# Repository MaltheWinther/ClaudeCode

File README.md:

# ClaudeCode

Testing Claude Code integration with GitHub.

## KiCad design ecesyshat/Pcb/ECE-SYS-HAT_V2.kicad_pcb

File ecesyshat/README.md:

# EceSysHat

This repo contains material for the ECE SYS HAT with the following devices:

* Six push-buttons
* Three LEDs
* An OLED Display
* An BMI160 Accelerometer / Gyro

### Documents

Contains pdf documentation, schematics

### PCB

Contains KiCad files for schematic and PCB

### TestPrograms

Contains small test programs to check correct assembly

Remember to enable i2c and spi with 'raspi_config' and install Libraries before running them. 

### Install Libraries 

#### Dependencies

To build and install the included libraries one needs to install some dependencies.

Run the following to install needed dependencies:

```bash
sudo apt update 
sudo apt install build-essential cmake git
```

#### Enabling i2c and spi 

As the oled screen communicates with the rpi using i2c, and the gyroscope communicates with the rpi using spi, one needs to enable those interfaces.

```bash
sudo raspi-config nonint do_i2c 0
sudo raspi-config nonint do_spi 0
```

#### Building and Installing

Enter Libraries dir:

```bash
cd Libraries/
```

You should now be able to run the following, to build and install the project.

```bash
cmake -S . -B build
cmake --build build
sudo cmake --install build --prefix /usr/
```

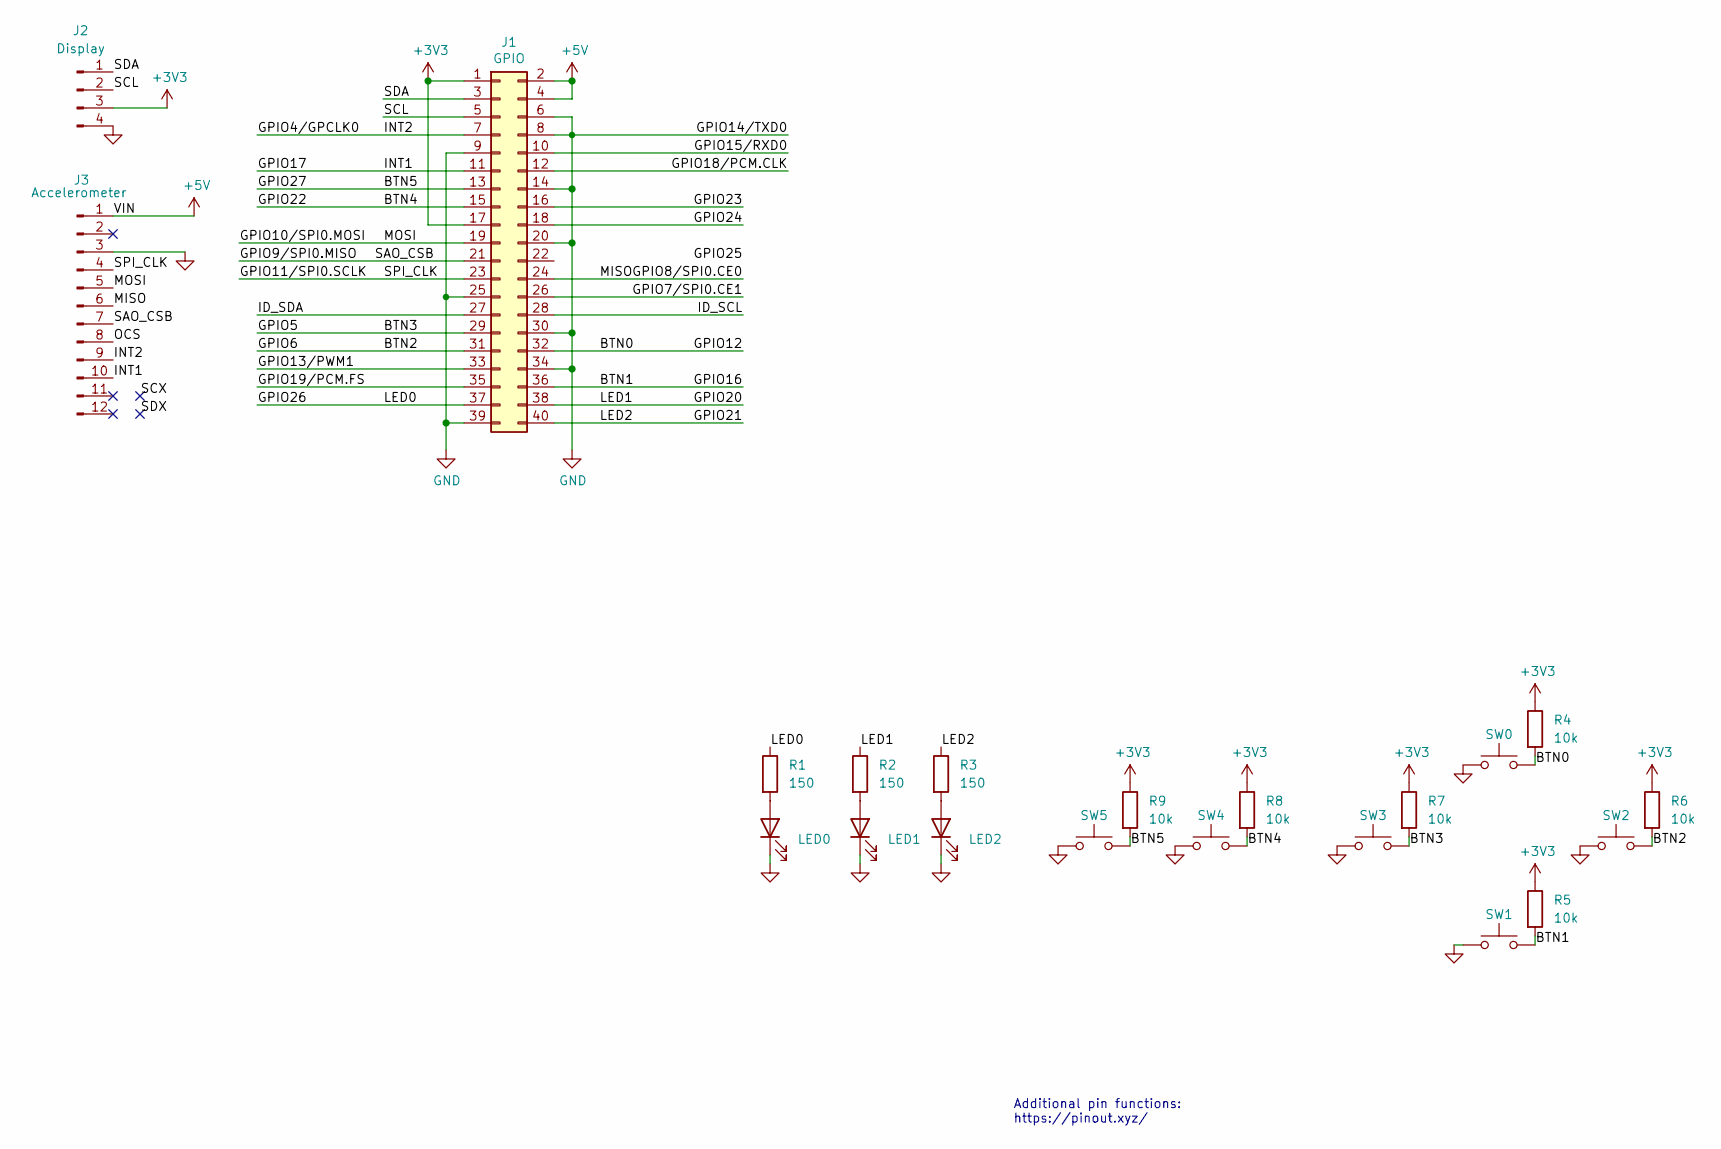
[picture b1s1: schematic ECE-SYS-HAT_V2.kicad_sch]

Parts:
J1: GPIO; PinSocket_2x20_P2.54mm_Vertical
J2: Display; SSD1306_OLED-0.91-128x32_BOB
J3: Accelerometer; GY-BMI160-BOB
LED0, LED1, LED2: LED; LED_D5.0mm
R1, R2, R3: 150; R_1206_3216Metric_Pad1.30x1.75mm_HandSolder
R4, R5, R6, R7, R8, R9: 10k; R_1206_3216Metric_Pad1.30x1.75mm_HandSolder
SW0, SW1, SW2, SW3, SW4, SW5: SW_Push; SW_PUSH_6mm_H5mm_2pin

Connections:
+3V3: J1.1, J1.17, J2.3, R4.1, R5.1, R6.1, R7.1, R8.1, R9.1
+5V: J1.2, J1.4, J3.1
/BTN0: J1.32, R4.2, SW0.2
/BTN1: J1.36, R5.2, SW1.2
/BTN2: J1.31, R6.2, SW2.2
/BTN3: J1.29, R7.2, SW3.2
/BTN4: J1.15, R8.2, SW4.2
/BTN5: J1.13, R9.2, SW5.2
/GPIO4/GPCLK0: J1.7, J3.9
/GPIO7/SPI0.CE1: J1.26
/GPIO8/SPI0.CE0: J1.24, J3.6
/GPIO9/SPI0.MISO: J1.21, J3.7
/GPIO10/SPI0.MOSI: J1.19, J3.5
/GPIO11/SPI0.SCLK: J1.23, J3.4
/GPIO13/PWM1: J1.33
/GPIO15/RXD0: J1.10
/GPIO17: J1.11, J3.10
/GPIO18/PCM.CLK: J1.12
/GPIO19/PCM.FS: J1.35
/GPIO20: J1.38, R2.1
/GPIO21: J1.40, R3.1
/GPIO23: J1.16
/GPIO24: J1.18
/GPIO26: J1.37, R1.1
/ID_SCL: J1.28
/ID_SDA: J1.27
/OCS: J3.8
/SCL: J1.5, J2.2
/SDA: J1.3, J2.1
GND: J1.6, J1.8, J1.9, J1.14, J1.20, J1.25, J1.30, J1.34, J1.39, J2.4, J3.3, LED0.1 (K), LED1.1 (K), LED2.1 (K), SW0.1, SW1.1, SW2.1, SW3.1, SW4.1, SW5.1
unnamed: LED0.2 (A), R1.2
unnamed: LED1.2 (A), R2.2
unnamed: LED2.2 (A), R3.2

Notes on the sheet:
Additional pin functions: https://pinout.xyz/

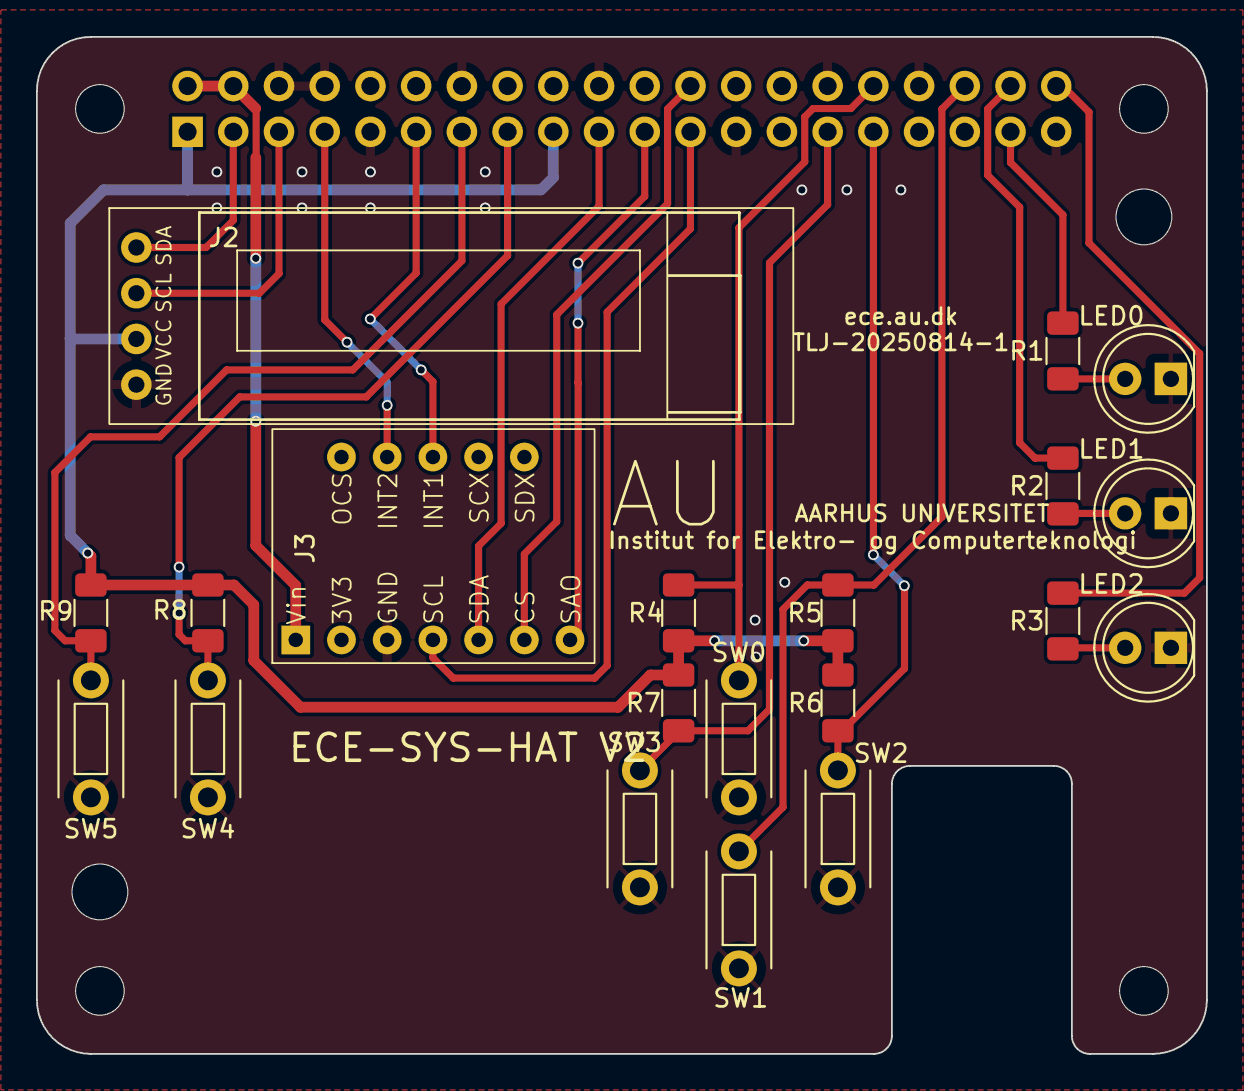
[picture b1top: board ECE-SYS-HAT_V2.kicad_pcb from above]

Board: 2 copper layers, 65.0 x 56.5 mm, 27 parts (1 on the bottom side), 23 nets.

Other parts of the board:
MH1, MH2, MH2#2, MH2#3, MH3, MH4: MountingHole_2.7mm_M2.5

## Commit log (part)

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2026-02-28 Added second level
